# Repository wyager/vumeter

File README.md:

# Nixie Tube Audio Meter

A full writeup is available [here](http://yager.io/vumeter/vu.html).

## Directory Structure
* schematics
    * tube-board - the board that powers and controls the nixie tubes
    * tube-offset-1,2 - PCBs that hold the tubes in place
    * audio-board - a teensy-based board that takes in S/PDIF audio over TOSLINK, does DSP, and outputs control data to the tube boards
    * custom - custom kicad parts for this project
    * case - freecad designs and macros for the case, plus some resultant SVGs I used to laser-cut the acrylic
    * bom - a list of some non-commodity part numbers
* code
    * audio-board - the code for the board that reads in S/PDIF audio over TOSLINK, does DSP, and controls the tube boards
    * linux-control - some code for controlling the tube boards from Linux/mac. Mostly used for testing.
    * test - used for testing the DSP code on desktop
    * tube-board - code for the board that powers/controls the bargraph tubes
    * vumeter-lib - hardware-independent code

## Building the code

Go into `code/audio_board` and `code/tube_board` and run `cargo build --release`. (Without `--release`, the binaries may be too large.)

## Uploading the code

First, build the code.

### Tube board

Go into `code/tube_board`.

Plug your AVR-ICE or similar JTAG programmer into the tube board via the programming header and run `./program.sh`.

### Audio Board

Go into `code/audio_board`.

Plug in your teensy over USB, put it in programming mode, and run `./program.sh`

## Building the PCBs

Get KiCad and open the schematics. How to export the schematics depends on your choice of PCB manufacturer. They should have instructions available online.

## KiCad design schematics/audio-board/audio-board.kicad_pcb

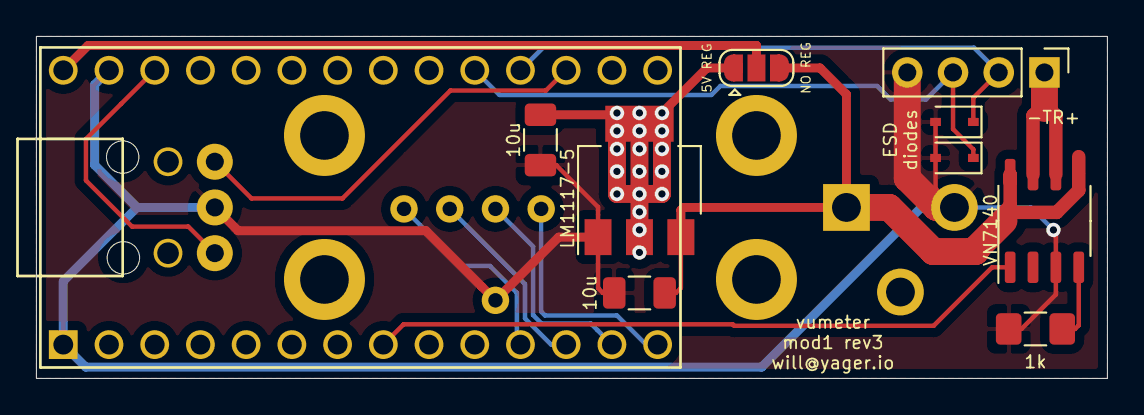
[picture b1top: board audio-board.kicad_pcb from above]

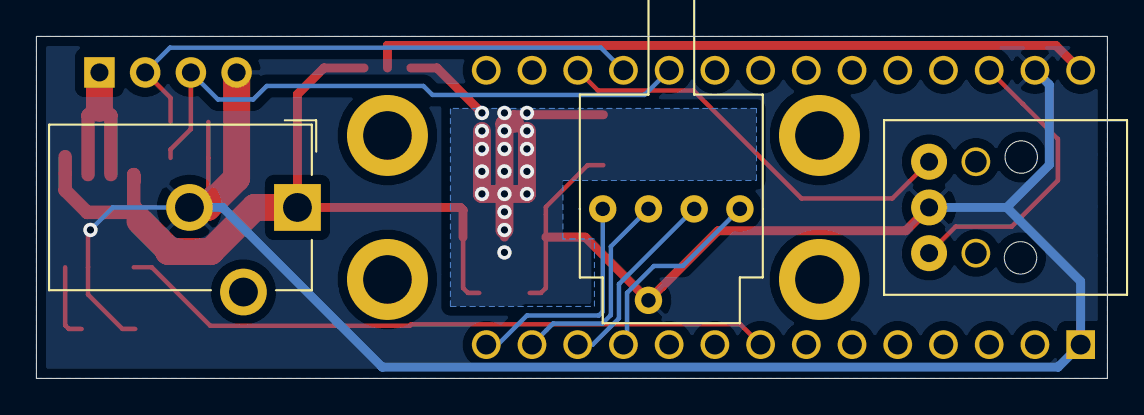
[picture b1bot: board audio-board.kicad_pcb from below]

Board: 2 copper layers, 59.5 x 19.0 mm, 17 parts (3 on the bottom side), 15 nets.

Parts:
C_pwr1, C_pwr2: 10u; C_1206_3216Metric
D1, D2: BZX384-xxx; D_SOD-323
H1, H2, H3, H4: MountingHole_Pad; MountingHole_2.7mm_M2.5_ISO14580_Pad
J3: Conn_01x04; PinHeader_1x04_P2.54mm_Vertical
J4: Conn_Coaxial_Power; BarrelJack_CUI_PJ-102AH_Horizontal
R1: 1k; R_1206_3216Metric_Pad1.42x1.75mm_HandSolder
SW1: 5V_BYPASS; SolderJumper-3_P1.3mm_Open_RoundedPad1.0x1.5mm
U1: Teensy4.0; Teensy40
U2: spdif_recv; Cliff_ORJ-8
U3: LM1117-5; SOT-223-3_TabPin2
U5: S-2151
U6: VN7140; SO-8_3.9x4.9mm_P1.27mm

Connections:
3V3: U1.31, U2.3
5V: C_pwr2.1, SW1.1, U3.2
GND: C_pwr1.1, C_pwr2.2, D1.2, D2.2, J3.4, J4.2, R1.1, U1.1, U1.32, U2.2, U3.1, U5.5, U6.3
unnamed: R1.2, U6.4
unnamed: U1.11, U5.4
unnamed: U1.12, U5.3
unnamed: U1.13, U5.2
unnamed: U1.14, U5.1
unnamed: U1.22, U2.1
TEENSY_5V_SUPPLY: SW1.2, U1.33
V_mid: C_pwr1.2, J4.1, SW1.3, U3.3, U6.5, U6.8
V_mid_out: J3.1, U6.6, U6.7
output_power_en: U1.8, U6.1
rx2: D2.1, J3.2, U1.23
tx2: D1.1, J3.3, U1.24

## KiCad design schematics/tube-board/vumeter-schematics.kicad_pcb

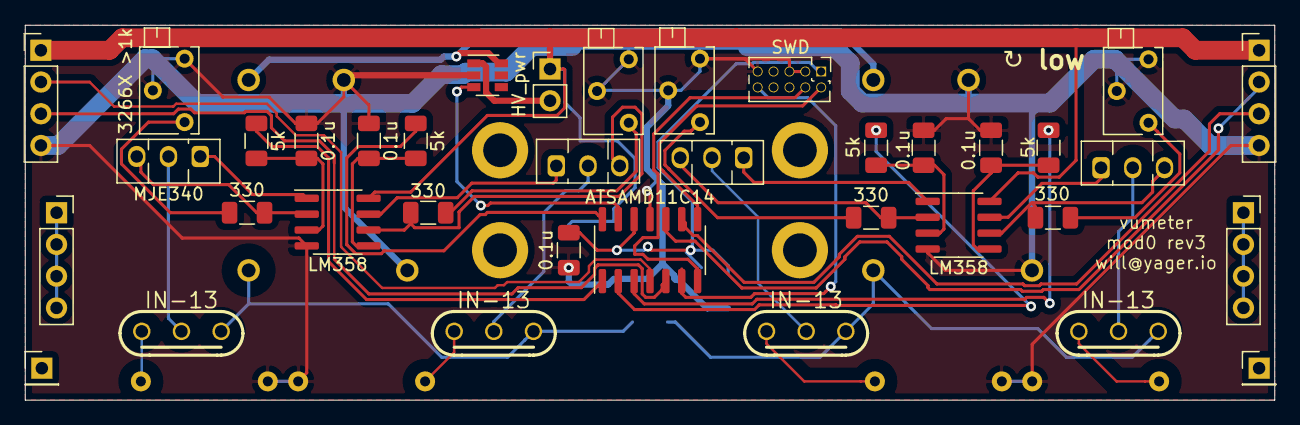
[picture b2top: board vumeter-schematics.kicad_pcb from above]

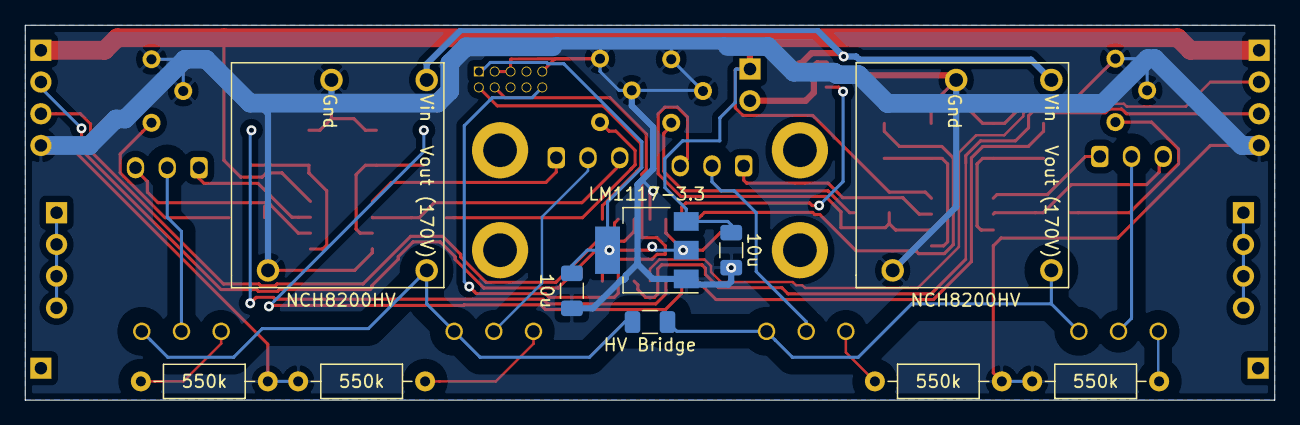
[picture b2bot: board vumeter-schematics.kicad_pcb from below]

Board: 2 copper layers, 100.0 x 30.0 mm, 51 parts (10 on the bottom side), 45 nets.

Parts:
C_decouple1: 0.1u; C_1206_3216Metric
C_pwm1, C_pwm2, C_pwm3, C_pwm4: 0.1u; C_1206_3216Metric
C_pwr1, C_pwr2: 10u; C_1206_3216Metric
H1, H2, H3, H4: MountingHole_Pad; MountingHole_2.7mm_M2.5_ISO14580_Pad
J1: SWD; PinHeader_2x05_P1.27mm_Vertical-smallholes
J2, J3: Conn_01x04; PinHeader_1x04_P2.54mm_Vertical
J4: Standoff_1; PinSocket_1x04_P2.54mm_Vertical
J5: Standoff_2; PinSocket_1x04_P2.54mm_Vertical
J6, J7: Conn_01x01_Male; PinHeader_1x01_P2.54mm_Vertical
JP1: HV Bridge; R_1206_3216Metric
JP2: HV_pwr; PinHeader_1x02_P2.54mm_Vertical
N1, N2, N3, N4: IN-13; fixed-IN-13-footprint-wide-sockets
Q1, Q2, Q3, Q4: MJE340; TO-126-3_Vertical-HV
R_Cathode1, R_Cathode2, R_Cathode3, R_Cathode4: 550k; R_Axial_DIN0207_L6.3mm_D2.5mm_P10.16mm_Horizontal
R_Sense1, R_Sense2, R_Sense3, R_Sense4: 330; R_1206_3216Metric
R_adj1, R_adj2, R_adj3, R_adj4: 3266X >1k; Potentiometer_Bourns_3266X_Horizontal
R_pwm1, R_pwm2, R_pwm3, R_pwm4: 5k; R_1206_3216Metric
U1, U4: LM358; SOIC-8_3.9x4.9mm_P1.27mm
U2: ATSAMD11C14; SOIC-14_3.9x8.7mm_P1.27mm
U3: LM1117-3.3; SOT-223-3_TabPin2
U5, U6: NCH8200HV
U7: TPS2281DBVR; SOT-23-6

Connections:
3V3: C_decouple1.1, C_pwr2.1, J1.1, U2.12, U3.2
GND: C_decouple1.2, C_pwm1.2, C_pwm2.2, C_pwm3.2, C_pwm4.2, C_pwr1.1, C_pwr2.2, J1.3, J1.5, J1.9, J2.4, J3.4, R_Cathode1.2, R_Cathode2.2, R_Cathode3.2, R_Cathode4.2, R_adj1.2, R_adj1.3, R_adj2.2, R_adj2.3, R_adj3.2, R_adj3.3, R_adj4.2, R_adj4.3, U1.4, U2.11, U3.1, U4.4, U5.2, U5.3, U6.2, U6.3, U7.2
HV1: JP1.2, N1.A, N2.A, U5.4
HV2: JP1.1, N3.A, N4.A, U6.4
M1: N1.K2, Q1.2
M2: N2.K2, Q2.2
M3: N3.K2, Q3.2
M4: N4.K2, Q4.2
M5: N1.K, R_Cathode1.1
M6: N2.K, R_Cathode2.1
M7: N3.K, R_Cathode3.1
M8: N4.K, R_Cathode4.1
unnamed: C_pwm1.1, R_pwm1.2, U1.3
unnamed: C_pwm2.1, R_pwm2.2, U1.5
unnamed: C_pwm3.1, R_pwm3.2, U4.3
unnamed: C_pwm4.1, R_pwm4.2, U4.5
unnamed: J4.1, J4.2, J4.3, J4.4
unnamed: J5.1, J5.2, J5.3, J5.4
unnamed: JP2.2, U7.1
unnamed: Q1.1, U1.1
unnamed: Q1.3, R_Sense1.1, U1.2
unnamed: Q2.1, U1.7
unnamed: Q2.3, R_Sense2.1, U1.6
unnamed: Q3.1, U4.1
unnamed: Q3.3, R_Sense3.1, U4.2
unnamed: Q4.1, U4.7
unnamed: Q4.3, R_Sense4.1, U4.6
unnamed: R_Sense1.2, R_adj1.1
unnamed: R_Sense2.2, R_adj2.1
unnamed: R_Sense3.2, R_adj3.1
unnamed: R_Sense4.2, R_adj4.1
unnamed: U5.1, U6.1, U7.6
PWM1: R_pwm1.1, U2.1
PWM2: R_pwm2.1, U2.14
PWM3: R_pwm3.1, U2.2
PWM4: R_pwm4.1, U2.3
V_mid: C_pwr1.2, J2.1, J3.1, JP2.1, U1.8, U3.3, U4.8
hv_en: U2.13, U7.3
rst: J1.10, U2.6
rx1: J2.2, U2.10
rx2: J3.3, U2.5
swclk: J1.4, U2.7
swdio: J1.2, U2.8
tx1: J2.3, U2.9
tx2: J3.2, U2.4

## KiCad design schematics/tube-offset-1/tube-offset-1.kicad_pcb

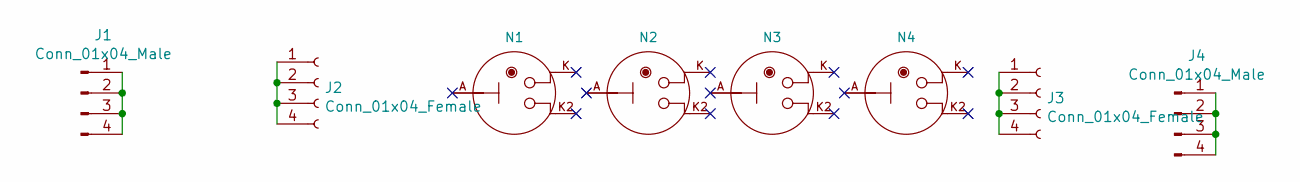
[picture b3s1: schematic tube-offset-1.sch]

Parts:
J1, J4: Conn_01x04_Male; PinSocket_1x04_P2.54mm_Vertical
J2, J3: Conn_01x04_Female; PinSocket_1x04_P2.54mm_Vertical
N1, N2, N3, N4: IN-13; fixed-IN-13-footprint

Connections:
unnamed: J1.1, J1.2, J1.3, J1.4
unnamed: J2.1, J2.2, J2.3, J2.4
unnamed: J3.1, J3.2, J3.3, J3.4
unnamed: J4.1, J4.2, J4.3, J4.4

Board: 2 copper layers, 8 parts (0 on the bottom side), 4 nets, no tracks yet.

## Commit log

2020-02-22 cleanup
2022-04-10 progress
2022-04-10 builds
2022-04-10 warnings
2022-04-10 some fixes
2023-03-15 svgs
2023-03-15 readme
2023-03-29 instr
2023-06-28 TODO.md
2023-06-28 lock
2023-07-13 update libraries and cargos
2023-07-13 small updates
2023-07-14 fix interrupt references
2023-07-14 compile and build + deploy
2023-07-14 add vumeter implementation
2023-07-15 remove debugging code
2023-07-16 add datasheets for various documentation and calculation. For IUC, good to have some info at hand
2023-07-29 move files as in original Will's structure
2023-07-29 update code and try debugging
2023-08-27 add library to display some info on an external display
2023-09-09 Initial commit for only rust code
2023-09-09 fix the NVIC prio and fix some compiler warnings
